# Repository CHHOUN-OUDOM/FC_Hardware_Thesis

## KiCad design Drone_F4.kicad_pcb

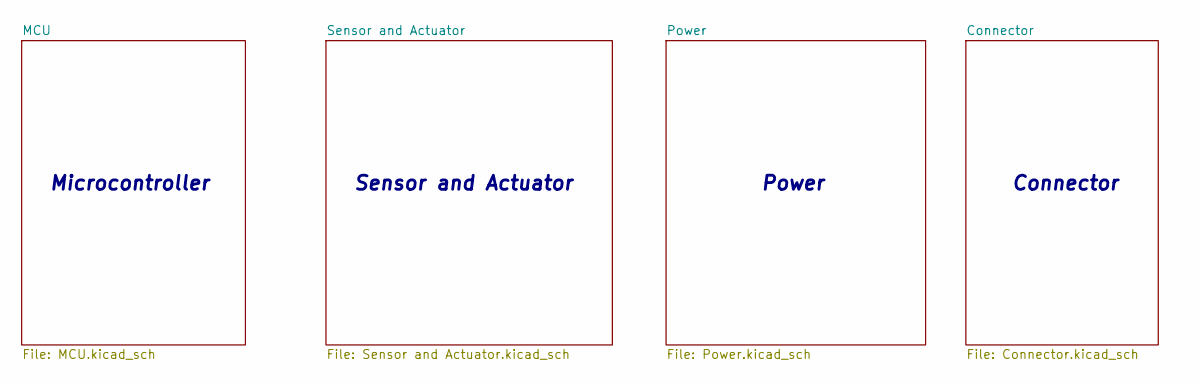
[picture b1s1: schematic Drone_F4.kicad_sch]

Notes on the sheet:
Power
Microcontroller
Sensor and Actuator
Connector

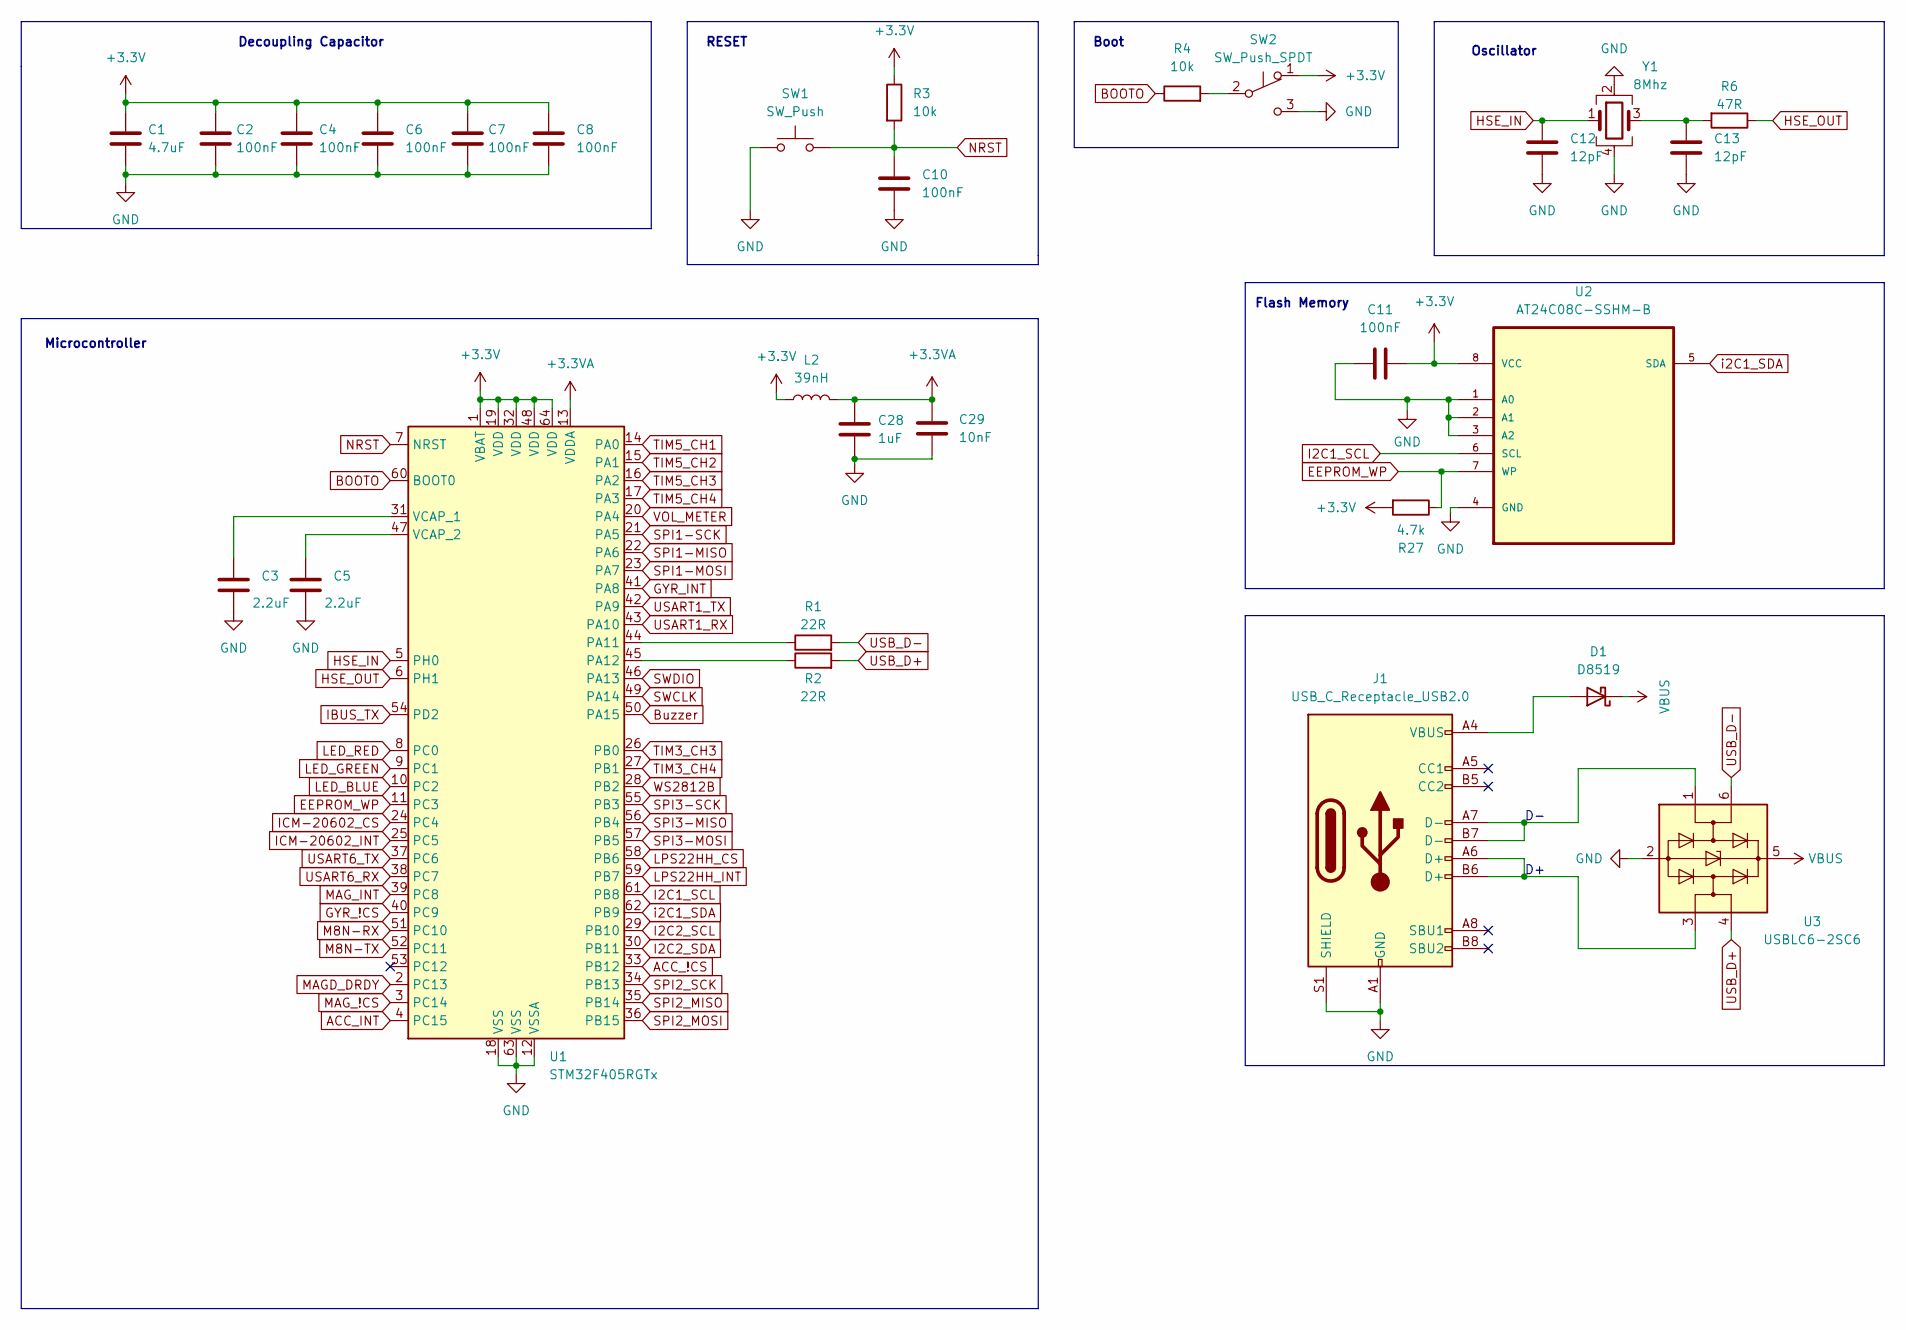
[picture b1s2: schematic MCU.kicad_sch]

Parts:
C1: 4.7uF; C_0603_1608Metric
C2, C4, C6, C7, C8, C10, C11: 100nF; C_0603_1608Metric
C3, C5: 2.2uF; C_0603_1608Metric
C12, C13: 12pF; C_0603_1608Metric
C28: 1uF; C_0603_1608Metric
C29: 10nF; C_0603_1608Metric
D1: D8519; D_SOD-123
J1: USB_C_Receptacle_USB2.0; USB_C_Receptacle_Palconn_UTC16-G
L2: 39nH; L_0603_1608Metric
R1, R2: 22R; R_0603_1608Metric
R3, R4: 10k; R_0603_1608Metric
R6: 47R; R_0603_1608Metric
R27: 4.7k; R_0603_1608Metric
SW1: SW_Push; SW_SPST_TL3305B
SW2: SW_Push_SPDT; SW_SPDT_PCM12
U1: STM32F405RGTx; LQFP-64_10x10mm_P0.5mm
U2: AT24C08C-SSHM-B; SOIC127P600X175-8N; MPN AT24C08C-SSHM-B
U3: USBLC6-2SC6; SOT-23-6
Y1: 8Mhz; Crystal_SMD_3225-4Pin_3.2x2.5mm

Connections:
+3.3VA: C28.1, C29.1, L2.2, U1.13 (VDDA)
+3V3: C1.1, C2.1, C4.1, C6.1, C7.1, C8.1, C11.2, L2.1, R3.1, R27.2, SW2.1 (A), U1.1 (VBAT), U1.19 (VDD), U1.32 (VDD), U1.48 (VDD), U1.64 (VDD), U2.8 (VCC); also elsewhere on the board
ACC_!CS: U1.33 (PB12); also elsewhere on the board
ACC_INT: U1.4 (PC15); also elsewhere on the board
BOOTO: R4.1, U1.60 (BOOT0)
Buzzer: U1.50 (PA15); also elsewhere on the board
EEPROM_WP: R27.1, U1.11 (PC3), U2.7 (WP)
GND: C1.2, C2.2, C3.2, C4.2, C5.2, C6.2, C7.2, C8.2, C10.2, C11.1, C12.2, C13.2, C28.2, C29.2, J1.A1 (GND), J1.A12 (GND), J1.B1 (GND), J1.B12 (GND), J1.S1 (SHIELD), SW1.1, SW2.3 (C), U1.12 (VSSA), U1.18 (VSS), U1.63 (VSS), U2.1 (A0), U2.2 (A1), U2.3 (A2), U2.4 (GND), U3.2 (GND), Y1.2, Y1.4; also elsewhere on the board
GYR_!CS: U1.40 (PC9); also elsewhere on the board
GYR_INT: U1.41 (PA8); also elsewhere on the board
HSE_IN: C12.1, U1.5 (PH0), Y1.1
HSE_OUT: R6.1, U1.6 (PH1)
I2C1_SCL: U1.61 (PB8), U2.6 (SCL); also elsewhere on the board
I2C2_SCL: U1.29 (PB10); also elsewhere on the board
I2C2_SDA: U1.30 (PB11); also elsewhere on the board
IBUS_TX: U1.54 (PD2); also elsewhere on the board
ICM-20602_CS: U1.24 (PC4); also elsewhere on the board
ICM-20602_INT: U1.25 (PC5); also elsewhere on the board
LED_BLUE: U1.10 (PC2); also elsewhere on the board
LED_GREEN: U1.9 (PC1); also elsewhere on the board
LED_RED: U1.8 (PC0); also elsewhere on the board
LPS22HH_CS: U1.58 (PB6); also elsewhere on the board
LPS22HH_INT: U1.59 (PB7); also elsewhere on the board
M8N-RX: U1.51 (PC10); also elsewhere on the board
M8N-TX: U1.52 (PC11); also elsewhere on the board
MAGD_DRDY: U1.2 (PC13); also elsewhere on the board
MAG_!CS: U1.3 (PC14); also elsewhere on the board
MAG_INT: U1.39 (PC8); also elsewhere on the board
NRST: C10.1, R3.2, SW1.2, U1.7 (NRST)
unnamed: C3.1, U1.31 (VCAP_1)
unnamed: C5.1, U1.47 (VCAP_2)
unnamed: C13.1, R6.2, Y1.3
unnamed: D1.2 (A), J1.A4 (VBUS), J1.A9 (VBUS), J1.B4 (VBUS), J1.B9 (VBUS)
unnamed: J1.A6 (D+), J1.B6 (D+), U3.3 (I/O2)
unnamed: J1.A7 (D-), J1.B7 (D-), U3.1 (I/O1)
unnamed: R1.1, U1.44 (PA11)
unnamed: R2.1, U1.45 (PA12)
unnamed: R4.2, SW2.2 (B)
SPI1-MISO: U1.22 (PA6); also elsewhere on the board
SPI1-MOSI: U1.23 (PA7); also elsewhere on the board
SPI1-SCK: U1.21 (PA5); also elsewhere on the board
SPI2_MISO: U1.35 (PB14); also elsewhere on the board
SPI2_MOSI: U1.36 (PB15); also elsewhere on the board
SPI2_SCK: U1.34 (PB13); also elsewhere on the board
SPI3-MISO: U1.56 (PB4); also elsewhere on the board
SPI3-MOSI: U1.57 (PB5); also elsewhere on the board
SPI3-SCK: U1.55 (PB3); also elsewhere on the board
SWCLK: U1.49 (PA14); also elsewhere on the board
SWDIO: U1.46 (PA13); also elsewhere on the board
TIM3_CH3: U1.26 (PB0); also elsewhere on the board
TIM3_CH4: U1.27 (PB1); also elsewhere on the board
TIM5_CH1: U1.14 (PA0); also elsewhere on the board
TIM5_CH2: U1.15 (PA1); also elsewhere on the board
TIM5_CH3: U1.16 (PA2); also elsewhere on the board
TIM5_CH4: U1.17 (PA3); also elsewhere on the board
USART1_RX: U1.43 (PA10); also elsewhere on the board
USART1_TX: U1.42 (PA9); also elsewhere on the board
USART6_RX: U1.38 (PC7); also elsewhere on the board
USART6_TX: U1.37 (PC6); also elsewhere on the board
USB_D+: R2.2, U3.4 (I/O2)
USB_D-: R1.2, U3.6 (I/O1)
VBUS: D1.1 (K), U3.5 (VBUS); also elsewhere on the board
VOL_METER: U1.20 (PA4); also elsewhere on the board
WS2812B: U1.28 (PB2); also elsewhere on the board
i2C1_SDA: U1.62 (PB9), U2.5 (SDA); also elsewhere on the board

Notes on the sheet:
Decoupling Capacitor
Flash Memory
RESET
Oscillator
Microcontroller
Boot

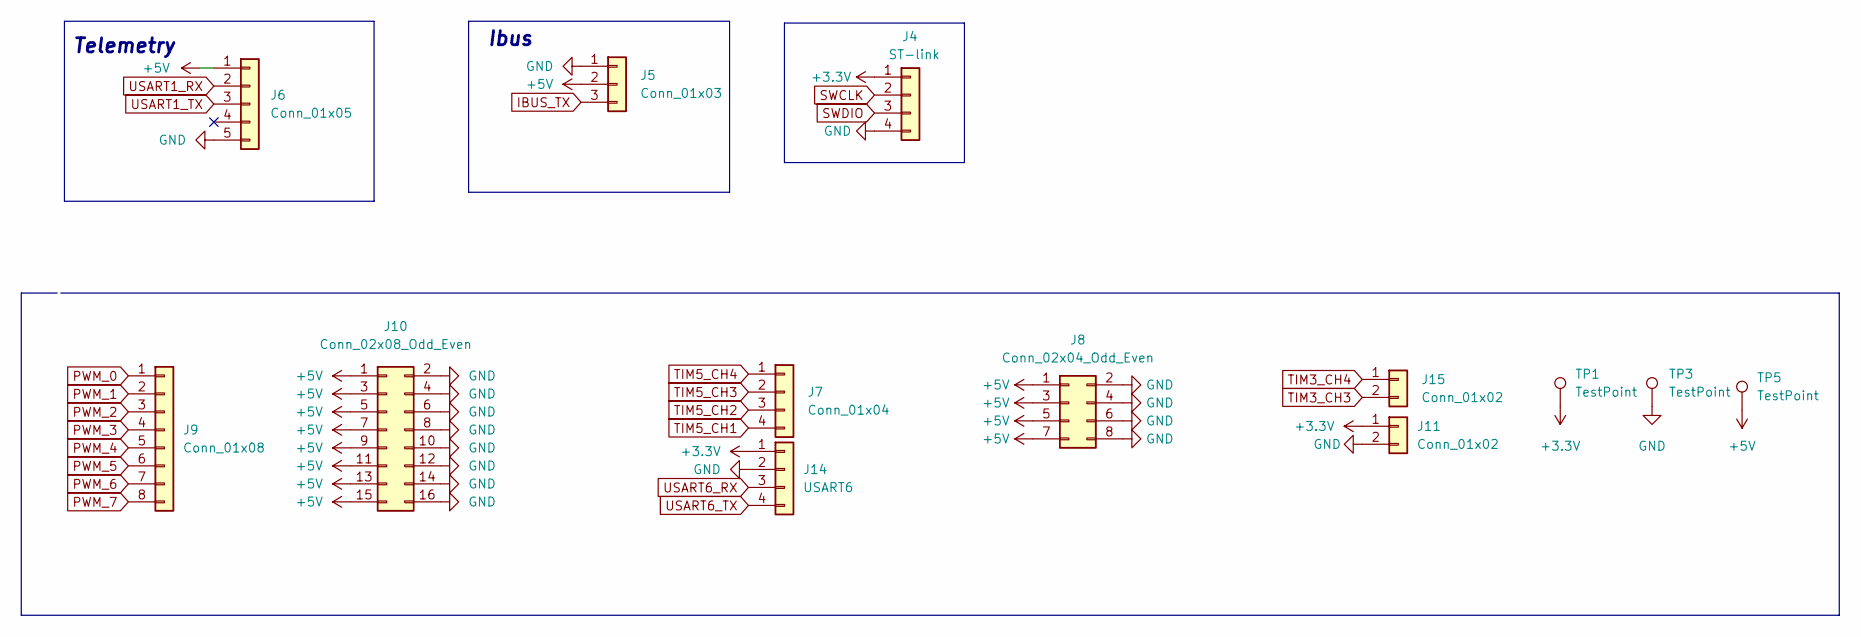
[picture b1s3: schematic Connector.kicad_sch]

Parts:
J4: ST-link; JST_XH_B4B-XH-A_1x04_P2.50mm_Vertical
J5: Conn_01x03; JST_XH_B3B-XH-A_1x03_P2.50mm_Vertical
J6: Conn_01x05; JST_XH_B5B-XH-A_1x05_P2.50mm_Vertical
J7: Conn_01x04; PinHeader_1x04_P2.54mm_Vertical
J8: Conn_02x04_Odd_Even; PinHeader_2x04_P2.54mm_Vertical
J9: Conn_01x08; PinHeader_1x08_P2.54mm_Vertical
J10: Conn_02x08_Odd_Even; PinHeader_2x08_P2.54mm_Vertical
J11, J15: Conn_01x02; PinHeader_1x02_P2.54mm_Vertical
J14: USART6; JST_XH_B4B-XH-A_1x04_P2.50mm_Vertical
TP1, TP3, TP5: TestPoint; TestPoint_Pad_D1.0mm

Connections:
+3V3: J4.1, J11.1, J14.1, TP1.1; also elsewhere on the board
+5V: J5.2, J6.1, J8.1, J8.3, J8.5, J8.7, J10.1, J10.3, J10.5, J10.7, J10.9, J10.11, J10.13, J10.15, TP5.1; also elsewhere on the board
GND: J4.4, J5.1, J6.5, J8.2, J8.4, J8.6, J8.8, J10.2, J10.4, J10.6, J10.8, J10.10, J10.12, J10.14, J10.16, J11.2, J14.2, TP3.1; also elsewhere on the board
IBUS_TX: J5.3; also elsewhere on the board
PWM_0: J9.1; also elsewhere on the board
PWM_1: J9.2; also elsewhere on the board
PWM_2: J9.3; also elsewhere on the board
PWM_3: J9.4; also elsewhere on the board
PWM_4: J9.5; also elsewhere on the board
PWM_5: J9.6; also elsewhere on the board
PWM_6: J9.7; also elsewhere on the board
PWM_7: J9.8; also elsewhere on the board
SWCLK: J4.2; also elsewhere on the board
SWDIO: J4.3; also elsewhere on the board
TIM3_CH3: J15.2; also elsewhere on the board
TIM3_CH4: J15.1; also elsewhere on the board
TIM5_CH1: J7.4; also elsewhere on the board
TIM5_CH2: J7.3; also elsewhere on the board
TIM5_CH3: J7.2; also elsewhere on the board
TIM5_CH4: J7.1; also elsewhere on the board
USART1_RX: J6.2; also elsewhere on the board
USART1_TX: J6.3; also elsewhere on the board
USART6_RX: J14.3; also elsewhere on the board
USART6_TX: J14.4; also elsewhere on the board

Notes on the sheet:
Telemetry
Ibus

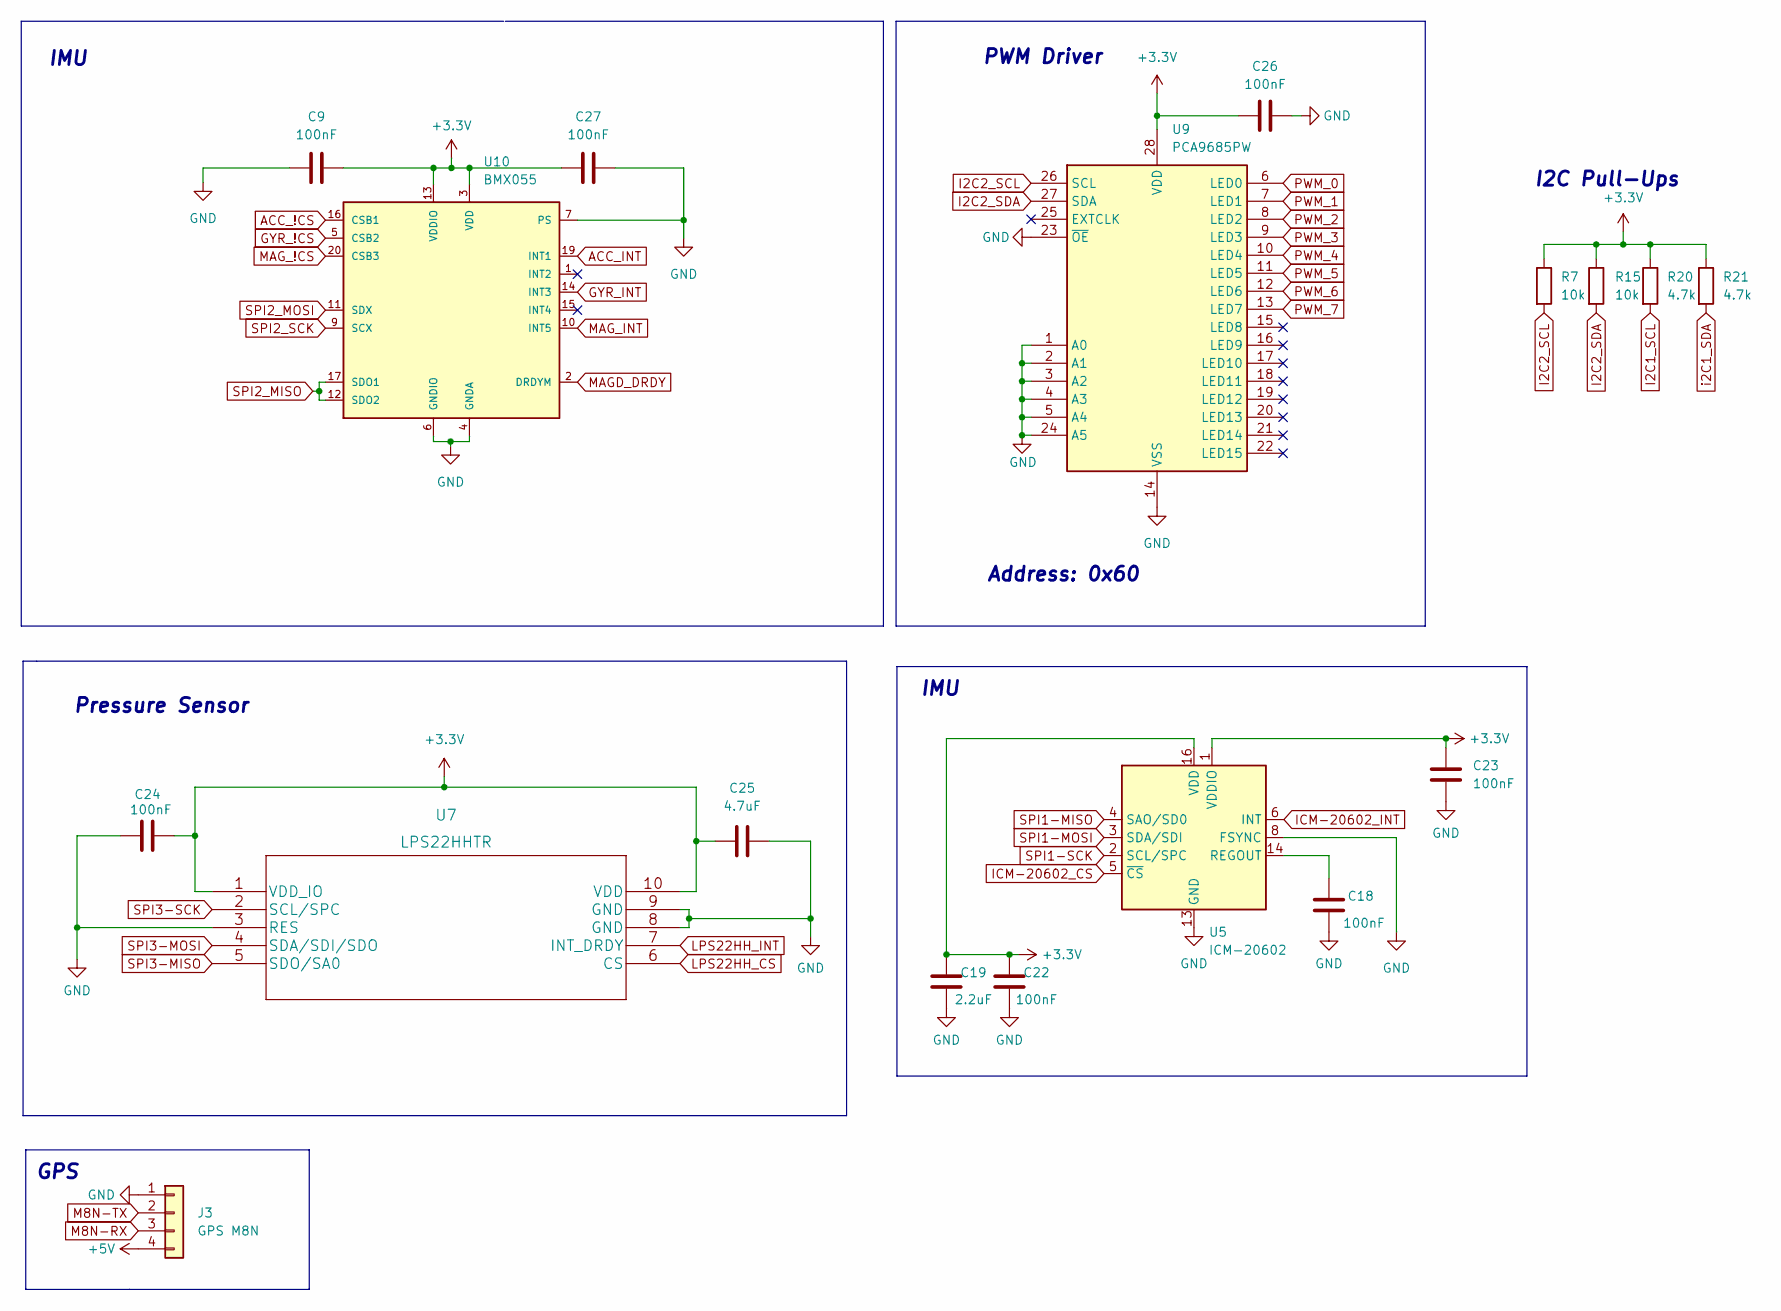
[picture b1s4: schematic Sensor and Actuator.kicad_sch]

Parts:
C9, C18, C22, C23, C24, C26, C27: 100nF; C_0603_1608Metric
C19: 2.2uF; C_0603_1608Metric
C25: 4.7uF; C_0603_1608Metric
J3: GPS M8N; JST_XH_B4B-XH-A_1x04_P2.50mm_Vertical
R7, R15: 10k; R_0603_1608Metric
R20, R21: 4.7k; R_0603_1608Metric
U5: ICM-20602; LGA-16_3x3mm_P0.5mm_LayoutBorder3x5y
U7: LPS22HHTR
U9: PCA9685PW; TSSOP-28_4.4x9.7mm_P0.65mm
U10: BMX055

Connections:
+3V3: C9.2, C19.1, C22.1, C23.1, C24.1, C25.2, C26.1, C27.1, R7.1, R15.1, R20.1, R21.1, U5.1 (VDDIO), U5.16 (VDD), U7.1 (VDD_IO), U7.10 (VDD), U9.28 (VDD), U10.3 (VDD), U10.13 (VDDIO); also elsewhere on the board
+5V: J3.4; also elsewhere on the board
ACC_!CS: U10.16 (CSB1); also elsewhere on the board
ACC_INT: U10.19 (INT1); also elsewhere on the board
GND: C9.1, C18.1, C19.2, C22.2, C23.2, C24.2, C25.1, C26.2, C27.2, J3.1, U5.8 (FSYNC), U5.9 (GND), U5.10 (GND), U5.11 (GND), U5.12 (GND), U5.13 (GND), U5.15 (GND), U7.3 (RES), U7.8 (GND), U7.9 (GND), U9.1 (A0), U9.2 (A1), U9.3 (A2), U9.4 (A3), U9.5 (A4), U9.14 (VSS), U9.23 (~OE), U9.24 (A5), U10.4 (GNDA), U10.6 (GNDIO), U10.7 (PS); also elsewhere on the board
GYR_!CS: U10.5 (CSB2); also elsewhere on the board
GYR_INT: U10.14 (INT3); also elsewhere on the board
I2C1_SCL: R20.2; also elsewhere on the board
I2C2_SCL: R7.2, U9.26 (SCL); also elsewhere on the board
I2C2_SDA: R15.2, U9.27 (SDA); also elsewhere on the board
ICM-20602_CS: U5.5 (~CS); also elsewhere on the board
ICM-20602_INT: U5.6 (INT); also elsewhere on the board
LPS22HH_CS: U7.6 (CS); also elsewhere on the board
LPS22HH_INT: U7.7 (INT_DRDY); also elsewhere on the board
M8N-RX: J3.3; also elsewhere on the board
M8N-TX: J3.2; also elsewhere on the board
MAGD_DRDY: U10.2 (DRDYM); also elsewhere on the board
MAG_!CS: U10.20 (CSB3); also elsewhere on the board
MAG_INT: U10.10 (INT5); also elsewhere on the board
unnamed: C18.2, U5.14 (REGOUT)
PWM_0: U9.6 (LED0); also elsewhere on the board
PWM_1: U9.7 (LED1); also elsewhere on the board
PWM_2: U9.8 (LED2); also elsewhere on the board
PWM_3: U9.9 (LED3); also elsewhere on the board
PWM_4: U9.10 (LED4); also elsewhere on the board
PWM_5: U9.11 (LED5); also elsewhere on the board
PWM_6: U9.12 (LED6); also elsewhere on the board
PWM_7: U9.13 (LED7); also elsewhere on the board
SPI1-MISO: U5.4 (SAO/SD0); also elsewhere on the board
SPI1-MOSI: U5.3 (SDA/SDI); also elsewhere on the board
SPI1-SCK: U5.2 (SCL/SPC); also elsewhere on the board
SPI2_MISO: U10.12 (SDO2), U10.17 (SDO1); also elsewhere on the board
SPI2_MOSI: U10.11 (SDX); also elsewhere on the board
SPI2_SCK: U10.9 (SCX); also elsewhere on the board
SPI3-MISO: U7.5 (SDO/SA0); also elsewhere on the board
SPI3-MOSI: U7.4 (SDA/SDI/SDO); also elsewhere on the board
SPI3-SCK: U7.2 (SCL/SPC); also elsewhere on the board
i2C1_SDA: R21.2; also elsewhere on the board

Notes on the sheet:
IMU
I2C Pull-Ups
Pressure Sensor
PWM Driver
Address: 0x60
GPS

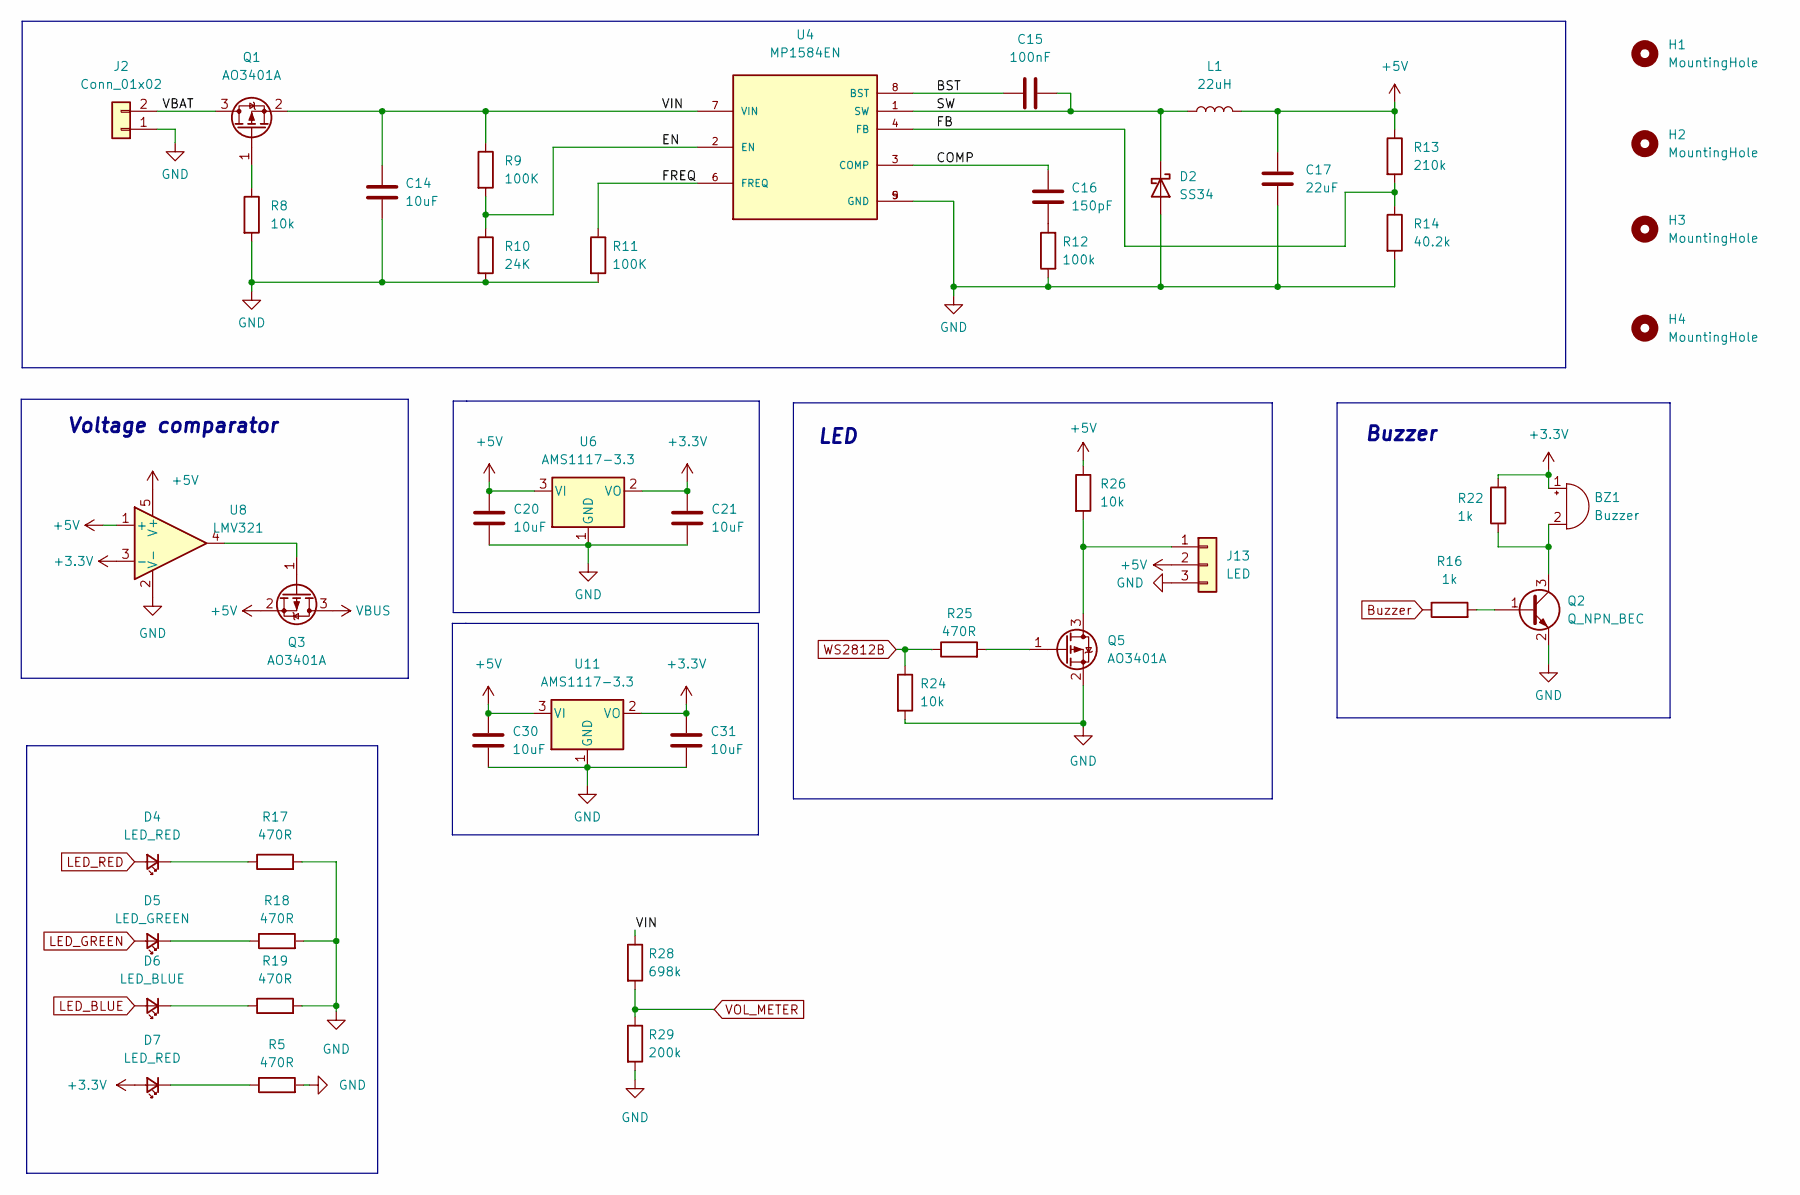
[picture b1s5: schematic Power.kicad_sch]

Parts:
BZ1: Buzzer; Buzzer_12x9.5RM7.6
C14: 10uF; C_1206_3216Metric
C15: 100nF; C_0603_1608Metric
C16: 150pF; C_0603_1608Metric
C17: 22uF; C_1206_3216Metric
C20, C21, C30, C31: 10uF; C_0805_2012Metric
D2: SS34; D_SMA
D4, D7: LED_RED; LED_0603_1608Metric
D5: LED_GREEN; LED_0603_1608Metric
D6: LED_BLUE; LED_0603_1608Metric
H1, H2, H3, H4: MountingHole; MountingHole_3.2mm_M3_Pad_Via
J2: Conn_01x02; PinHeader_1x02_P2.54mm_Vertical
J13: LED; JST_XH_B3B-XH-A_1x03_P2.50mm_Vertical
L1: 22uH; L_7.3x7.3_H4.5
Q1, Q3: AO3401A; SOT23
Q2: Q_NPN_BEC; SOT-23
Q5: AO3401A; SOT-23
R5, R17, R18, R19, R25: 470R; R_0603_1608Metric
R8, R24, R26: 10k; R_0603_1608Metric
R9, R11: 100K; R_0603_1608Metric
R10: 24K; R_0603_1608Metric
R12: 100k; R_0603_1608Metric
R13: 210k; R_0603_1608Metric
R14: 40.2k; R_0603_1608Metric
R16, R22: 1k; R_0603_1608Metric
R28: 698k; R_0603_1608Metric
R29: 200k; R_0603_1608Metric
U4: MP1584EN; SOIC127P600X170-9N
U6, U11: AMS1117-3.3; SOT-89-3
U8: LMV321; SOT-23-5

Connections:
+3V3: BZ1.1 (-), C21.1, C31.1, D7.2 (A), R22.2, U6.2 (VO), U8.3 (-), U11.2 (VO); also elsewhere on the board
+5V: C17.1, C20.1, C30.1, J13.2, L1.2, Q3.2 (S), R13.1, R26.1, U6.3 (VI), U8.1 (+), U8.5 (V+), U11.3 (VI); also elsewhere on the board
/Power/BST: C15.1, U4.8 (BST)
/Power/COMP: C16.1, U4.3 (COMP)
/Power/EN: R9.2, R10.1, U4.2 (EN)
/Power/FB: R13.2, R14.1, U4.4 (FB)
/Power/FREQ: R11.1, U4.6 (FREQ)
/Power/SW: C15.2, D2.1 (K), L1.1, U4.1 (SW)
/Power/VBAT: J2.2, Q1.3 (D)
/Power/VIN: C14.1, Q1.2 (S), R9.1, R28.1, U4.7 (VIN)
Buzzer: R16.1; also elsewhere on the board
GND: C14.2, C17.2, C20.2, C21.2, C30.2, C31.2, D2.2 (A), J2.1, J13.3, Q2.2 (E), Q5.2 (S), R5.2, R8.2, R10.2, R11.2, R12.1, R14.2, R17.2, R18.2, R19.2, R24.2, R29.2, U4.5 (GND), U4.9 (GND), U6.1 (GND), U8.2 (V-), U11.1 (GND); also elsewhere on the board
LED_BLUE: D6.2 (A); also elsewhere on the board
LED_GREEN: D5.2 (A); also elsewhere on the board
LED_RED: D4.2 (A); also elsewhere on the board
unnamed: BZ1.2 (+), Q2.3 (C), R22.1
unnamed: C16.2, R12.2
unnamed: D4.1 (K), R17.1
unnamed: D5.1 (K), R18.1
unnamed: D6.1 (K), R19.1
unnamed: D7.1 (K), R5.1
unnamed: J13.1, Q5.3 (D), R26.2
unnamed: Q1.1 (G), R8.1
unnamed: Q2.1 (B), R16.2
unnamed: Q3.1 (G), U8.4
unnamed: Q5.1 (G), R25.2
VBUS: Q3.3 (D); also elsewhere on the board
VOL_METER: R28.2, R29.1; also elsewhere on the board
WS2812B: R24.1, R25.1; also elsewhere on the board

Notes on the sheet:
LED
Buzzer
Voltage comparator

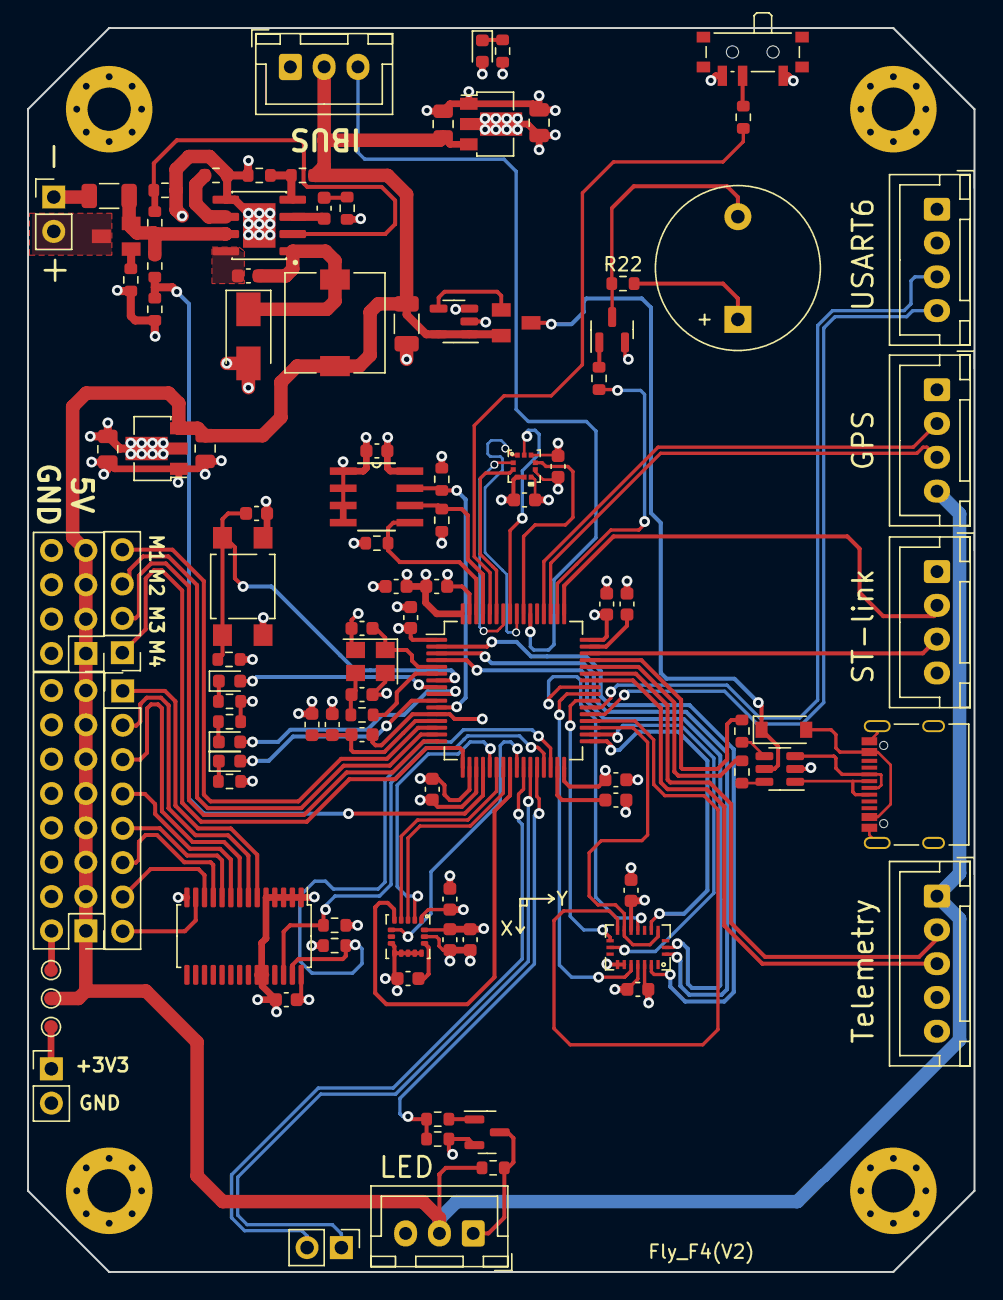
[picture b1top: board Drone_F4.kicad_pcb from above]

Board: 4 copper layers, 70.0 x 92.0 mm, 107 parts (0 on the bottom side), 94 nets.
